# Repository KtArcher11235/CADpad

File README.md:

# CADpad
A hackpad designed for cad
<br>

<br>

## rationale
I needed a macropad to help with cad designing, eg, usefull and cimple keys that you dont even think about like ctrl and shift etc.
<br>
I used onshape and kicad for the designs, and decided on a cool rugged ish look.
<br>
## specifications
  BOM:  
1x Seeed XIAO RP2040  
6x Cherry MX Switches  
6x Blank DSA keycaps (White)  
6x SK6812 MINI-E LEDs  
4x M3x16mm screws  
optional (4x M3x5mx4mm heatset inserts)  
  OTHERS:  
firmware  
3d prints  
## schematic 
  <br>
## pcb
 <br> 
## case

## assembly
1. put in the heatset inserts
2. put the pcb in (glue is youe friend.)
3. screw the lid on
4. upload firmware
5. its that easy

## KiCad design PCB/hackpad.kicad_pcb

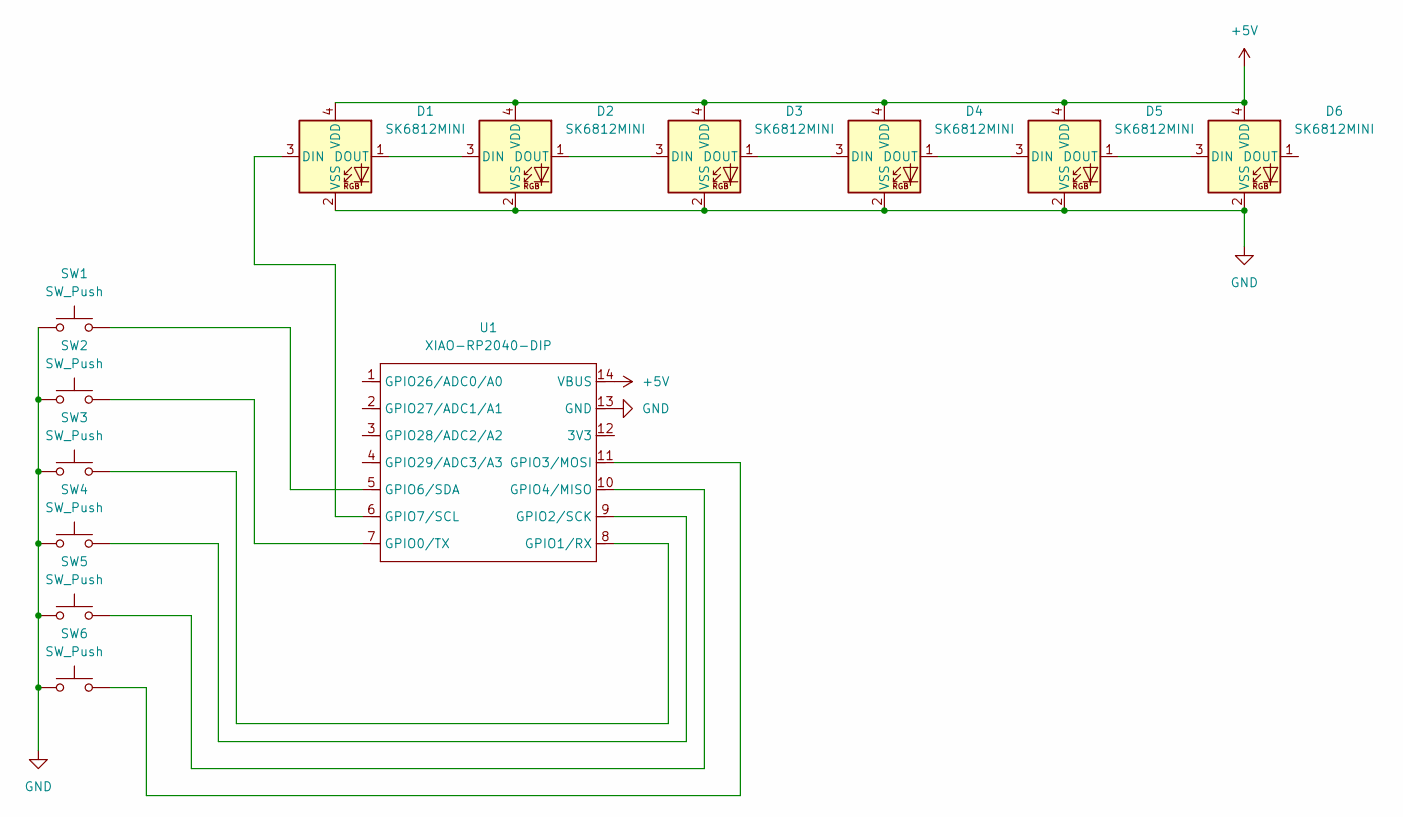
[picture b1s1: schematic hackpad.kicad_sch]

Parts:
D1, D2, D3, D4, D5, D6: SK6812MINI; SK6812-MINI-E
SW1, SW2, SW3, SW4, SW5, SW6: SW_Push; SW_Cherry_MX_1.00u_PCB
U1: XIAO-RP2040-DIP

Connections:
+5V: D1.4 (VDD), D2.4 (VDD), D3.4 (VDD), D4.4 (VDD), D5.4 (VDD), D6.4 (VDD), U1.14 (VBUS)
GND: D1.2 (VSS), D2.2 (VSS), D3.2 (VSS), D4.2 (VSS), D5.2 (VSS), D6.2 (VSS), SW1.1, SW2.1, SW3.1, SW4.1, SW5.1, SW6.1, U1.13 (GND)
unnamed: D1.3 (DIN), U1.6 (GPIO7/SCL)
unnamed: D1.1 (DOUT), D2.3 (DIN)
unnamed: D2.1 (DOUT), D3.3 (DIN)
unnamed: D3.1 (DOUT), D4.3 (DIN)
unnamed: D4.1 (DOUT), D5.3 (DIN)
unnamed: D5.1 (DOUT), D6.3 (DIN)
unnamed: SW2.2, U1.7 (GPIO0/TX)
unnamed: SW3.2, U1.8 (GPIO1/RX)
unnamed: SW4.2, U1.9 (GPIO2/SCK)
unnamed: SW6.2, U1.11 (GPIO3/MOSI)
unnamed: SW5.2, U1.10 (GPIO4/MISO)
unnamed: SW1.2, U1.5 (GPIO6/SDA)

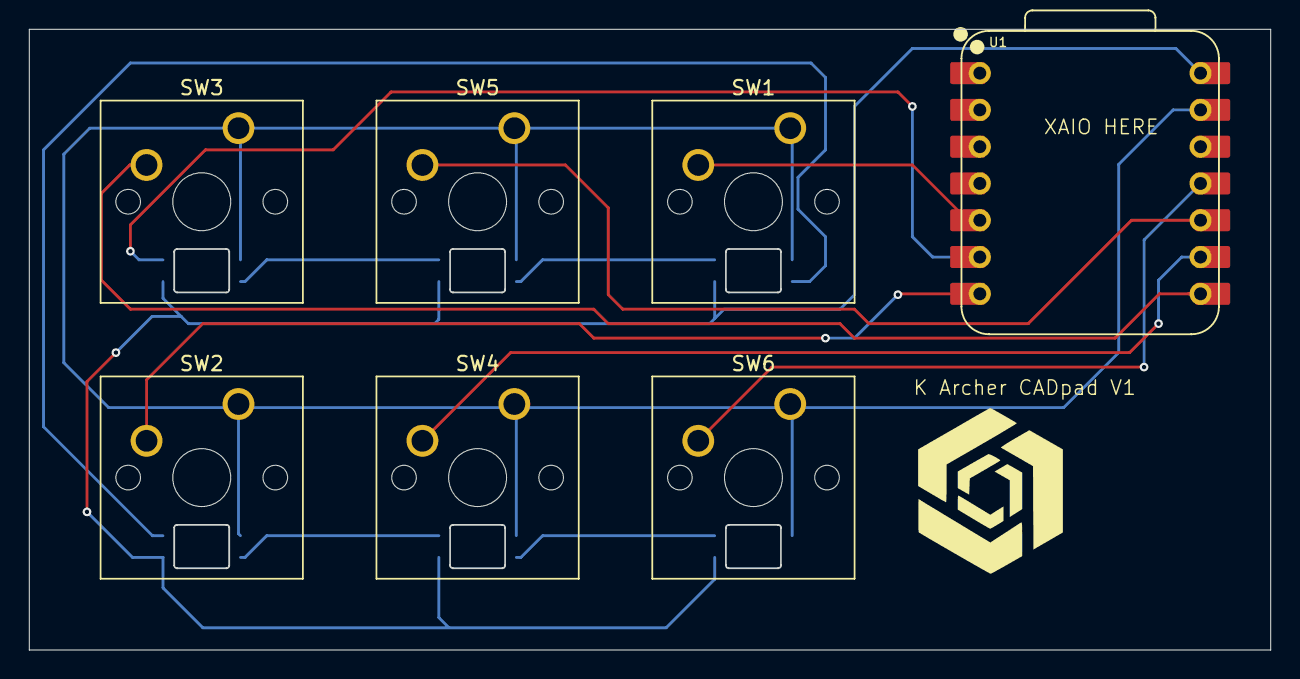
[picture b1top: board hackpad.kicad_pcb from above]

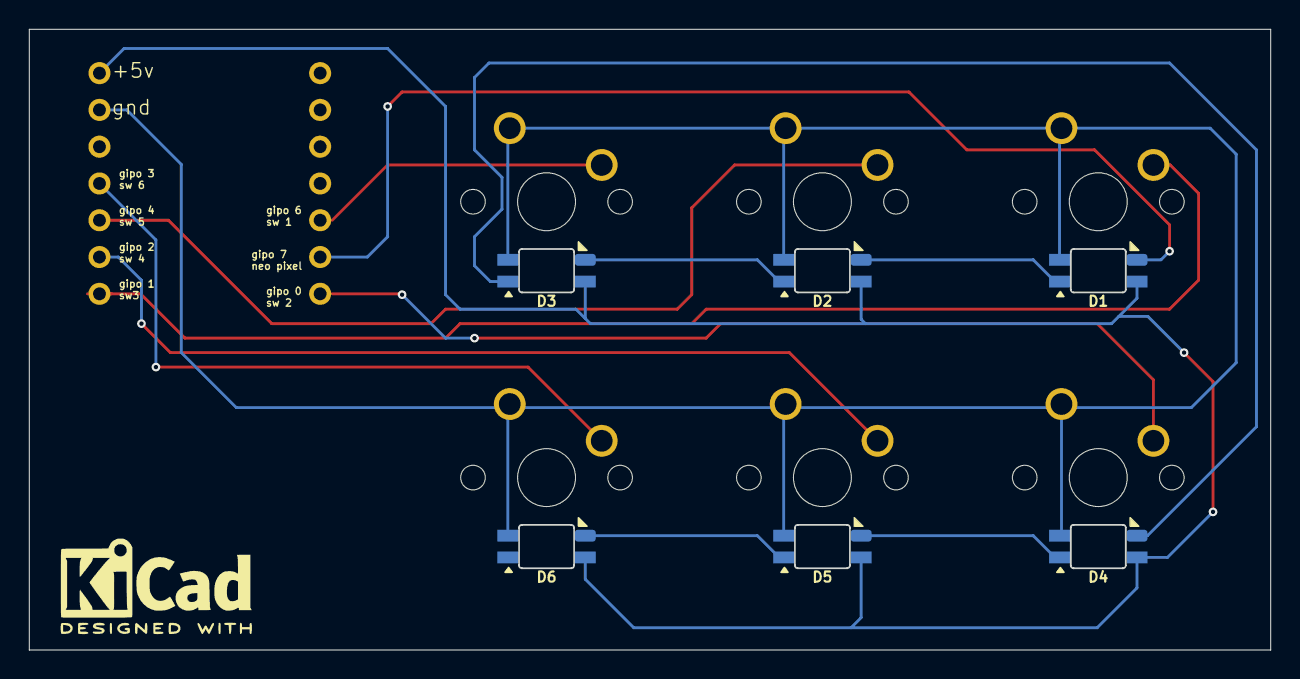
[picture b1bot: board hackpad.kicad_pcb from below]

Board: 2 copper layers, 85.7 x 42.8 mm, 13 parts (6 on the bottom side), 14 nets.

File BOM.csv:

"Id";"Designator";"Footprint";"Quantity";"Designation";"Supplier and ref";
1;"SW2,SW4,SW3,SW6,SW1,SW5";"SW_Cherry_MX_1.00u_PCB";6;"SW_Push";;;
2;"U1";"XIAO-RP2040-DIP";1;"XIAO-RP2040-DIP";;;
3;"D6,D3,D4,D2,D5,D1";"SK6812-MINI-E";6;"SK6812MINI";;;

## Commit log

2025-12-17 Add initial hardware and firmware files
    Added CAD STEP file, CircuitPython firmware, KMK firmware zip, and main.py script. Updated README.md to reflect new files and setup instructions.
2025-12-17 Add initial KiCad PCB, schematic, and project files
    Added hackpad.kicad_pcb, hackpad.kicad_sch, and hackpad.kicad_pro files for the Hackpad project. These files define the PCB layout, schematic, and project configuration, including footprints for Cher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
2025-12-17 Expand README with project details and images
    Added rationale, specifications, and images for CADpad.
2025-12-17 Add BOM and 3D print files for project enclosure
    Added BOM.csv listing components and two STL files (top and bottom) for 3D printing the enclosure. These files support assembly and fabrication of the hardware.
2026-02-03 Enhance README with assembly steps
    Added assembly instructions for macropad setup.
